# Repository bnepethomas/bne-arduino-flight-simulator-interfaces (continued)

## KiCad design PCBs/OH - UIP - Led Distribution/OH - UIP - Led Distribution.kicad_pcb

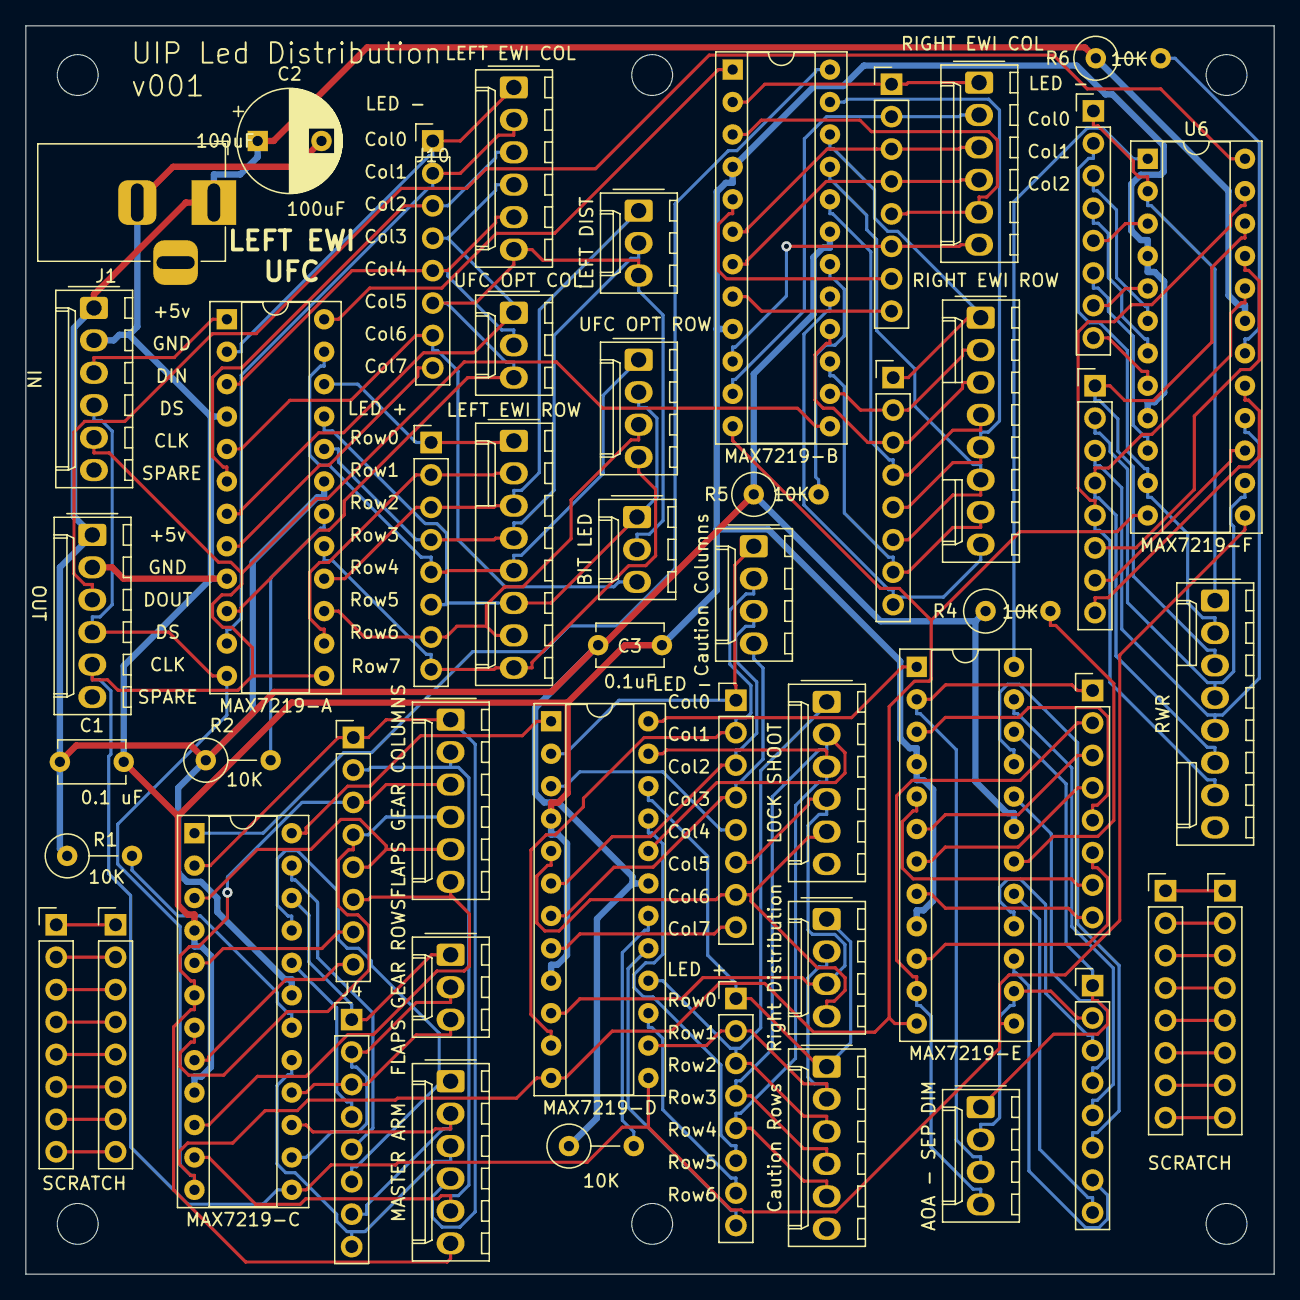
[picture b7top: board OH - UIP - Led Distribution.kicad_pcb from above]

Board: 2 copper layers, 97.8 x 97.8 mm, 57 parts (0 on the bottom side), 129 nets.

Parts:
C1, C3: 0.1uF; C_Disc_D5.1mm_W3.2mm_P5.00mm
C2: 100uF; CP_Radial_D8.0mm_P5.00mm
H1, H2, H3, H4, H5, H6: MountingHole; MountingHole_3.2mm_M3
J1: Conn_01x02_Female; BarrelJack_Horizontal
J2, J3: Molex_1x06_P2.54mm_Vertical
J4, J5, J9, J10, J16, J17, J23, J24, J26, J27, J30, J31, J32, J33, J35, J36: PinHeader_1x08_P2.54mm_Vertical
J6: FLAPS GEAR COLUMNS; Molex_1x06_P2.54mm_Vertical
J7: FLAPS GEAR ROWS; Molex_1x03_P2.54mm_Vertical
J8: MASTER ARM; Molex_1x06_P2.54mm_Vertical
J11: LEFT EWI ROW; Molex_1x08_P2.54mm_Vertical
J12: LEFT EWI COL; Molex_1x06_P2.54mm_Vertical
J13: UFC OPT COL; Molex_1x03_P2.54mm_Vertical
J14: UFC OPT ROW; Molex_1x04_P2.54mm_Vertical
J15: BIT LED; Molex_1x03_P2.54mm_Vertical
J18: Right Distribution; Molex_1x04_P2.54mm_Vertical
J19: LOCK SHOOT; Molex_1x06_P2.54mm_Vertical
J20: Caution Columns; Molex_1x04_P2.54mm_Vertical
J21: Caution Rows; Molex_1x06_P2.54mm_Vertical
J22: LEFT DIST; Molex_1x03_P2.54mm_Vertical
J25: AOA - SEP DIM; Molex_1x04_P2.54mm_Vertical
J28: RIGHT EWI ROW; Molex_1x08_P2.54mm_Vertical
J29: RIGHT EWI COL; Molex_1x06_P2.54mm_Vertical
J34: RWR; Molex_1x08_P2.54mm_Vertical
R1, R2, R3, R4, R5, R6: 10K; R_Axial_DIN0309_L9.0mm_D3.2mm_P5.08mm_Vertical
U1: MAX7219-C; DIP-24_W7.62mm_Socket
U2: MAX7219-A; DIP-24_W7.62mm_Socket
U3: MAX7219-D; DIP-24_W7.62mm_Socket
U4: MAX7219-E; DIP-24_W7.62mm_Socket
U5: MAX7219-B; DIP-24_W7.62mm_Socket
U6: MAX7219-F; DIP-24_W7.62mm_Socket

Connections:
+5V: C1.1, C2.1, C3.1, J1.1, J2.1, J3.1, R1.1, R2.1, R3.1, R4.1, R5.1, R6.1, U1.19, U2.19, U3.19, U4.19, U5.19, U6.19
/A-DOUT-B-DIN: U2.24, U5.1
/ACol0: J10.1, J12.1, U2.2
/ACol1: J10.2, J12.2, U2.11
/ACol2: J10.3, J12.3, U2.6
/ACol3: J10.4, J12.4, J13.1, U2.7
/ACol4: J10.5, J12.5, J13.2, U2.3
/ACol5: J10.6, J12.6, J13.3, J15.2, J22.3, U2.10
/ACol6: J10.7, J15.3, U2.5
/ACol7: J10.8, U2.8
/ARow0: J9.1, J11.1, U2.22
/ARow1: J9.2, J11.2, U2.14
/ARow2: J9.3, J11.3, J22.1, U2.16
/ARow3: J9.4, J11.4, J22.2, U2.20
/ARow4: J9.5, J11.5, J14.1, U2.23
/ARow5: J9.6, J11.6, J14.2, J15.1, U2.21
/ARow6: J9.7, J11.7, J14.3, U2.15
/ARow7: J9.8, J11.8, J14.4, U2.17
/B-DOUT-C-DIN: U1.1, U5.24
/BCol0: J27.1, J29.1, U5.2
/BCol1: J27.2, J29.2, U5.11
/BCol2: J27.3, J29.3, U5.6
/BCol3: J27.4, J29.4, U5.7
/BCol4: J27.5, J29.5, U5.3
/BCol5: J27.6, J29.6, U5.10
/BCol6: J27.7, U5.5
/BCol7: J27.8, U5.8
/BRow0: J26.1, J28.1, U5.22
/BRow1: J26.2, J28.2, U5.14
/BRow2: J26.3, J28.3, U5.16
/BRow3: J26.4, J28.4, U5.20
/BRow4: J26.5, J28.5, U5.23
/BRow5: J26.6, J28.6, U5.21
/BRow6: J26.7, J28.7, U5.15
/BRow7: J26.8, J28.8, U5.17
/C-DOUT-D-DIN: U1.24, U3.1
/CCol0: J5.1, J6.1, J8.4, U1.2
/CCol1: J5.2, J6.2, J8.5, U1.11
/CCol2: J5.3, J6.3, J8.6, U1.6
/CCol3: J5.4, J6.4, U1.7
/CCol4: J5.5, J6.5, U1.3
/CCol5: J5.6, J6.6, U1.10
/CCol6: J5.7, U1.5
/CCol7: J5.8, U1.8
/CLK: J2.5, J3.5, U1.13, U2.13, U3.13, U4.13, U5.13, U6.13
/CRow0: J4.1, J7.1, U1.22
/CRow1: J4.2, J7.2, U1.14
/CRow2: J4.3, J7.3, U1.16
/CRow3: J4.4, U1.20
/CRow4: J4.5, U1.23
/CRow5: J4.6, J8.1, U1.21
/CRow6: J4.7, J8.2, U1.15
/CRow7: J4.8, J8.3, U1.17
/D-DOUT-E-DIN: U3.24, U4.1
/DCol0: J16.1, J20.1, U3.2
/DCol1: J16.2, J20.2, U3.11
/DCol2: J16.3, J20.3, U3.6
/DCol3: J16.4, J20.4, U3.7
/DCol4: J16.5, U3.3
/DCol5: J16.6, J18.3, J19.4, U3.10
/DCol6: J16.7, J18.4, J19.5, U3.5
/DCol7: J16.8, U3.8
/DIN: J2.3, U2.1
/DOUT: J3.3, U6.24
/DRow0: J17.1, J18.1, J21.1, U3.22
/DRow1: J17.2, J18.2, J21.2, U3.14
/DRow2: J17.3, J19.1, J21.3, U3.16
/DRow3: J17.4, J19.2, J21.4, U3.20
/DRow4: J17.5, J19.3, J21.5, U3.23
/DRow5: J17.6, U3.21
/DRow6: J17.7, U3.15
/DRow7: J17.8, U3.17
/E-DOUT-F-DIN: U4.24, U6.1
/ECol0: J23.1, J25.3, U4.2
/ECol1: J23.2, J25.4, U4.11
/ECol2: J23.3, U4.6
/ECol3: J23.4, U4.7
/ECol4: J23.5, U4.3
/ECol5: J23.6, U4.10
/ECol6: J23.7, U4.5
/ECol7: J23.8, U4.8
/ERow0: J24.1, J25.1, U4.22
/ERow1: J24.2, J25.2, U4.14
/ERow2: J24.3, U4.16
/ERow3: J24.4, U4.20
/ERow4: J24.5, U4.23
/ERow5: J24.6, U4.21
/ERow6: J24.7, U4.15
/ERow7: J24.8, U4.17
/FCol0: J32.1, J34.1, U6.2
/FCol1: J32.2, J34.2, U6.11
/FCol2: J32.3, U6.6
/FCol3: J32.4, U6.7
/FCol4: J32.5, U6.3
/FCol5: J32.6, U6.10
/FCol6: J32.7, U6.5
/FCol7: J32.8, U6.8
/FRow0: J33.1, J34.3, U6.22
/FRow1: J33.2, J34.4, U6.14
/FRow2: J33.3, J34.5, U6.16
/FRow3: J33.4, J34.6, U6.20
/FRow4: J33.5, J34.7, U6.23
/FRow5: J33.6, U6.21
/FRow6: J33.7, U6.15
/FRow7: J33.8, U6.17
/LOAD: J2.4, J3.4, U1.12, U2.12, U3.12, U4.12, U5.12, U6.12
GND: C1.2, C2.2, C3.2, J1.2, J2.2, J3.2, U1.4, U1.9, U2.4, U2.9, U3.4, U3.9, U4.4, U4.9, U5.4, U5.9, U6.4, U6.9
unnamed: J30.1, J31.1
unnamed: J30.2, J31.2
unnamed: J30.3, J31.3
unnamed: J30.4, J31.4
unnamed: J30.5, J31.5
unnamed: J30.6, J31.6
unnamed: J30.7, J31.7
unnamed: J30.8, J31.8
unnamed: J35.1, J36.1
unnamed: J35.2, J36.2
unnamed: J35.3, J36.3
unnamed: J35.4, J36.4
unnamed: J35.5, J36.5
unnamed: J35.6, J36.6
unnamed: J35.7, J36.7
unnamed: J35.8, J36.8
unnamed: R1.2, U1.18
unnamed: R2.2, U2.18
unnamed: R3.2, U3.18
unnamed: R4.2, U4.18
unnamed: R5.2, U5.18
unnamed: R6.2, U6.18

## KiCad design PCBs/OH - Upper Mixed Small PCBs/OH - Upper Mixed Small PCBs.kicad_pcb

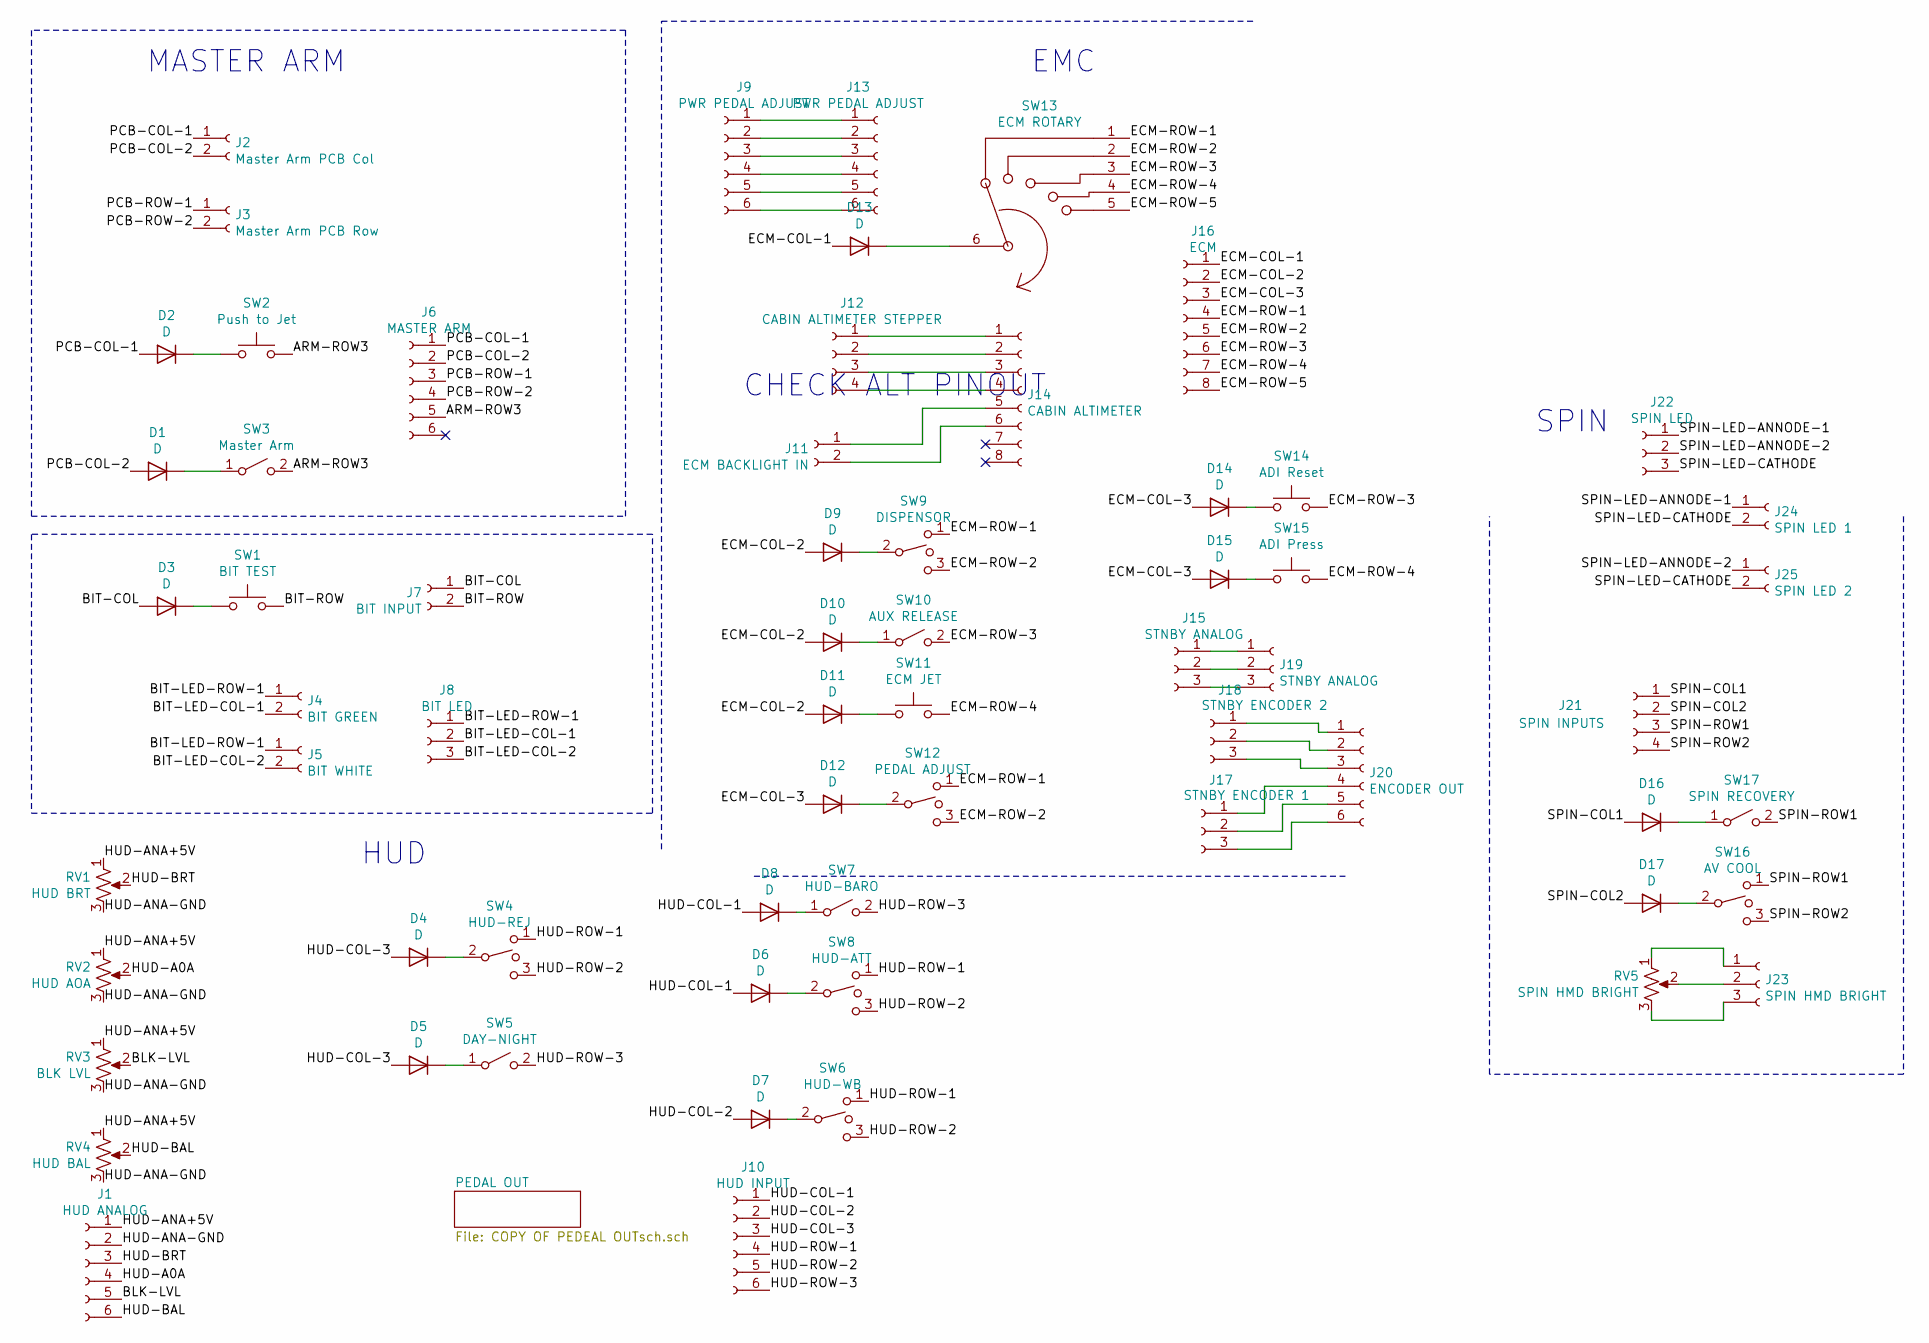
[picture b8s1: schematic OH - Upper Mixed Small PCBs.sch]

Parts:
D1, D2, D3, D4, D5, D6, D7, D8, D9, D10, D11, D12, D13, D14, D15, D16, D17: D; D_Signal_P7.62mm_Horizontal
J1: HUD ANALOG; Molex_1x06_P2.54mm_Vertical
J2: Master Arm PCB Col; Molex_1x02_P2.54mm_Vertical
J3: Master Arm PCB Row; Molex_1x02_P2.54mm_Vertical
J4: BIT GREEN; Molex_1x02_P2.54mm_Vertical
J5: BIT WHITE; Molex_1x02_P2.54mm_Vertical
J6: MASTER ARM; Molex_1x06_P2.54mm_Vertical
J7: BIT INPUT; Molex_1x02_P2.54mm_Vertical
J8: BIT LED; Molex_1x03_P2.54mm_Vertical
J9, J13: PWR PEDAL ADJUST; Molex_1x06_P2.54mm_Vertical
J10: HUD INPUT; Molex_1x06_P2.54mm_Vertical
J11: ECM BACKLIGHT IN; Molex_1x02_P2.54mm_Vertical
J12: CABIN ALTIMETER STEPPER; Molex_1x04_P2.54mm_Vertical
J14: CABIN ALTIMETER; Molex_1x08_P2.54mm_Vertical
J15, J19: STNBY ANALOG; Molex_1x03_P2.54mm_Vertical
J16: ECM; Molex_1x08_P2.54mm_Vertical
J17: STNBY ENCODER 1; Molex_1x03_P2.54mm_Vertical
J18: STNBY ENCODER 2; Molex_1x03_P2.54mm_Vertical
J20: ENCODER OUT; Molex_1x06_P2.54mm_Vertical
J21: SPIN INPUTS; Molex_1x04_P2.54mm_Vertical
J22: SPIN LED; Molex_1x03_P2.54mm_Vertical
J23: SPIN HMD BRIGHT; Molex_1x03_P2.54mm_Vertical
J24: SPIN LED 1; Molex_1x02_P2.54mm_Vertical
J25: SPIN LED 2; Molex_1x02_P2.54mm_Vertical
RV1: HUD BRT; Molex_1x03_P2.54mm_Vertical
RV2: HUD AOA; Molex_1x03_P2.54mm_Vertical
RV3: BLK LVL; Molex_1x03_P2.54mm_Vertical
RV4: HUD BAL; Molex_1x03_P2.54mm_Vertical
RV5: SPIN HMD BRIGHT; Molex_1x03_P2.54mm_Vertical
SW1: BIT TEST; Molex_1x02_P2.54mm_Vertical
SW2: Push to Jet; Molex_1x02_P2.54mm_Vertical
SW3: Master Arm; Molex_1x02_P2.54mm_Vertical
SW4: HUD-REJ; Molex_1x03_P2.54mm_Vertical
SW5: DAY-NIGHT; Molex_1x02_P2.54mm_Vertical
SW6: HUD-WB; Molex_1x03_P2.54mm_Vertical
SW7: HUD-BARO; Molex_1x02_P2.54mm_Vertical
SW8: HUD-ATT; Molex_1x03_P2.54mm_Vertical
SW9: DISPENSOR; Molex_1x03_P2.54mm_Vertical
SW10: AUX RELEASE; Molex_1x02_P2.54mm_Vertical
SW11: ECM JET; Molex_1x02_P2.54mm_Vertical
SW12: PEDAL ADJUST; Molex_1x03_P2.54mm_Vertical
SW13: ECM ROTARY; Molex_1x06_P2.54mm_Vertical
SW14: ADI Reset; Molex_1x02_P2.54mm_Vertical
SW15: ADI Press; Molex_1x02_P2.54mm_Vertical
SW16: AV COOL; Molex_1x03_P2.54mm_Vertical
SW17: SPIN RECOVERY; Molex_1x02_P2.54mm_Vertical

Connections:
/ARM-ROW3: J6.5, SW2.2, SW3.2 (B)
/BIT-COL: D3.2 (A), J7.1
/BIT-LED-COL-1: J4.2, J8.2
/BIT-LED-COL-2: J5.2, J8.3
/BIT-LED-ROW-1: J4.1, J5.1, J8.1
/BIT-ROW: J7.2, SW1.2
/BLK-LVL: J1.5, RV3.2
/ECM-COL-1: D13.2 (A), J16.1
/ECM-COL-2: D9.2 (A), D10.2 (A), D11.2 (A), J16.2
/ECM-COL-3: D12.2 (A), D14.2 (A), D15.2 (A), J16.3
/ECM-ROW-1: J16.4, SW9.1, SW12.1, SW13.1
/ECM-ROW-2: J16.5, SW9.3, SW12.3, SW13.2
/ECM-ROW-3: J16.6, SW10.2 (B), SW13.3, SW14.2
/ECM-ROW-4: J16.7, SW11.2, SW13.4, SW15.2
/ECM-ROW-5: J16.8, SW13.5
/HUD-A0A: J1.4, RV2.2
/HUD-ANA+5V: J1.1, RV1.1, RV2.1, RV3.1, RV4.1
/HUD-ANA-GND: J1.2, RV1.3, RV2.3, RV3.3, RV4.3
/HUD-BAL: J1.6, RV4.2
/HUD-BRT: J1.3, RV1.2
/HUD-COL-1: D6.2 (A), D8.2 (A), J10.1
/HUD-COL-2: D7.2 (A), J10.2
/HUD-COL-3: D4.2 (A), D5.2 (A), J10.3
/HUD-ROW-1: J10.4, SW4.1, SW6.1, SW8.1
/HUD-ROW-2: J10.5, SW4.3, SW6.3, SW8.3
/HUD-ROW-3: J10.6, SW5.2 (B), SW7.2 (B)
/PCB-COL-1: D2.2 (A), J2.1, J6.1
/PCB-COL-2: D1.2 (A), J2.2, J6.2
/PCB-ROW-1: J3.1, J6.3
/PCB-ROW-2: J3.2, J6.4
/SPIN-COL1: D16.2 (A), J21.1
/SPIN-COL2: D17.2 (A), J21.2
/SPIN-LED-ANNODE-1: J22.1, J24.1
/SPIN-LED-ANNODE-2: J22.2, J25.1
/SPIN-LED-CATHODE: J22.3, J24.2, J25.2
/SPIN-ROW1: J21.3, SW16.1, SW17.2 (B)
/SPIN-ROW2: J21.4, SW16.3
unnamed: D1.1 (K), SW3.1 (A)
unnamed: D2.1 (K), SW2.1
unnamed: D3.1 (K), SW1.1
unnamed: D4.1 (K), SW4.2
unnamed: D5.1 (K), SW5.1 (A)
unnamed: D6.1 (K), SW8.2
unnamed: D7.1 (K), SW6.2
unnamed: D8.1 (K), SW7.1 (A)
unnamed: D9.1 (K), SW9.2
unnamed: D10.1 (K), SW10.1 (A)
unnamed: D11.1 (K), SW11.1
unnamed: D12.1 (K), SW12.2
unnamed: D13.1 (K), SW13.6
unnamed: D14.1 (K), SW14.1
unnamed: D15.1 (K), SW15.1
unnamed: D16.1 (K), SW17.1 (A)
unnamed: D17.1 (K), SW16.2
unnamed: J11.2, J14.6
unnamed: J12.1, J14.1
unnamed: J12.2, J14.2
unnamed: J12.3, J14.3
unnamed: J12.4, J14.4
unnamed: J9.1, J13.1
unnamed: J9.2, J13.2
unnamed: J9.3, J13.3
unnamed: J9.4, J13.4
unnamed: J9.5, J13.5
unnamed: J9.6, J13.6
unnamed: J15.1, J19.1
unnamed: J15.2, J19.2
unnamed: J15.3, J19.3
unnamed: J17.1, J20.4
unnamed: J17.2, J20.5
unnamed: J17.3, J20.6
unnamed: J18.1, J20.1
unnamed: J18.2, J20.2
unnamed: J18.3, J20.3
unnamed: J23.1, RV5.1
unnamed: J23.2, RV5.2
unnamed: J23.3, RV5.3

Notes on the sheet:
MASTER ARM
EMC
CHECK ALT PINOUT
SPIN
HUD

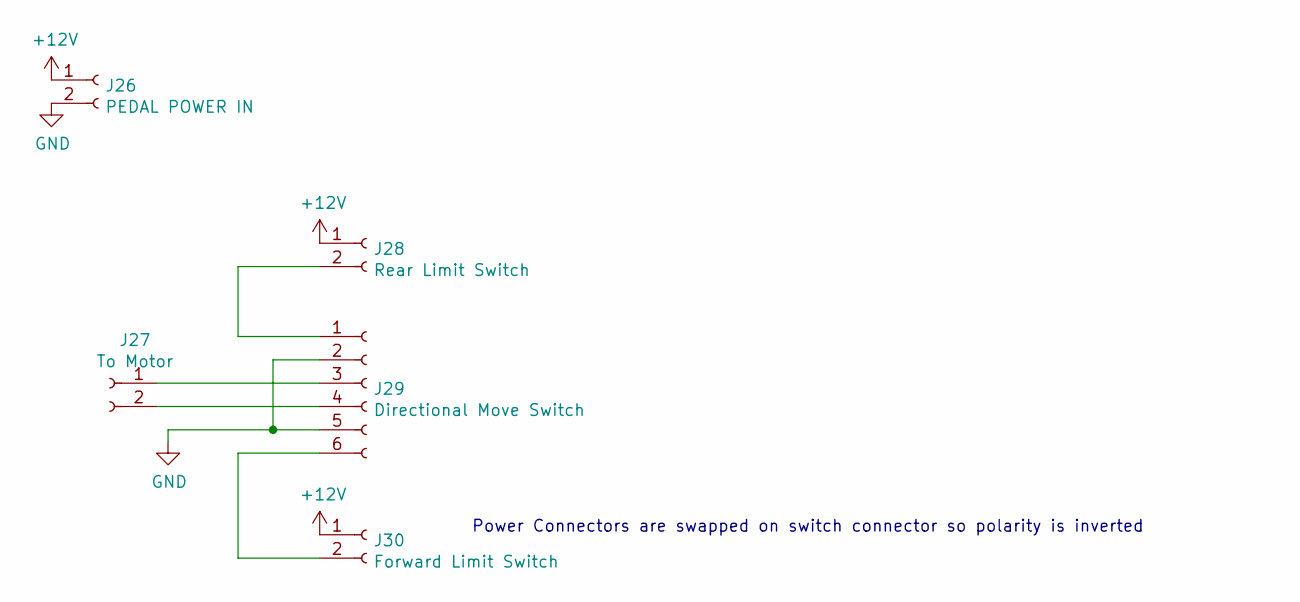
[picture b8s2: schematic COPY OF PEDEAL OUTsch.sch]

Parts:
J26: PEDAL POWER IN; Molex_1x02_P2.54mm_Vertical
J27: To Motor; Molex_1x02_P2.54mm_Vertical
J28: Rear Limit Switch; Molex_1x02_P2.54mm_Vertical
J29: Directional Move Switch; Molex_1x06_P2.54mm_Vertical
J30: Forward Limit Switch; Molex_1x02_P2.54mm_Vertical

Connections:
+12V: J26.1, J28.1, J30.1
GND: J26.2, J29.2, J29.5
unnamed: J27.1, J29.3
unnamed: J27.2, J29.4
unnamed: J28.2, J29.1
unnamed: J29.6, J30.2

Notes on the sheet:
Power Connectors are swapped on switch connector so polarity is inverted

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
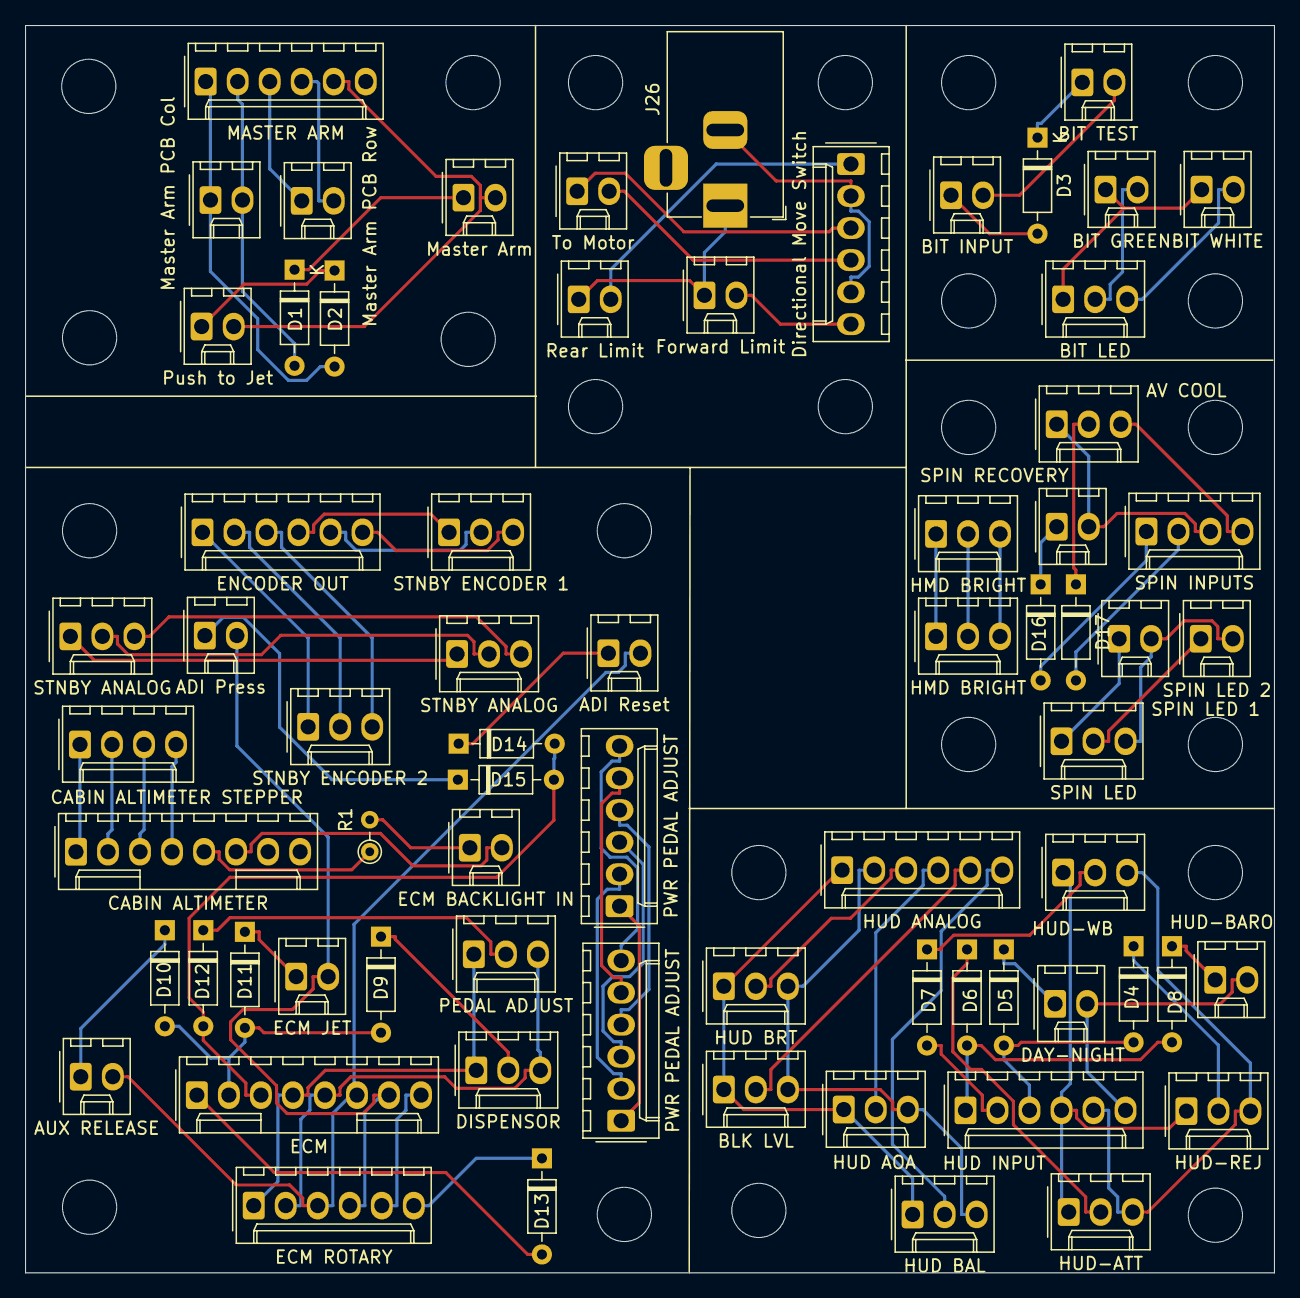
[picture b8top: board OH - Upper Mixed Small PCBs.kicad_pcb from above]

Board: 2 copper layers, 99.1 x 98.9 mm, 94 parts (0 on the bottom side), 85 nets.

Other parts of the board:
H1, H5, H8, H11, H12, H14, H15, H16, H17, H18, H19, H20, H21, H22, H23, H24, H25, H26, H27, H28, H29, H30, H31, H32: MountingHole; MountingHole_4.3mm_M4
R1: 1K; PT_R_Axial_DIN0204_L3.6mm_D1.6mm_P2.54mm_Vertical
